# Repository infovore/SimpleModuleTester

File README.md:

# WARNING

**I've never built or tested this. I don't recommend making one of these. It was noodling around.**

# Simple Module Tester

This is a simple Eurorack module tester that can be powered from 5V USB.

- It takes +5v from USB power, and turns it into +/-12v and also passes along the 5v. 
- The key component is a IR0512S DC-DC Converter from XP Power which [costs about £8.50 from Farnell](http://uk.farnell.com/xp-power/ir0512s/dc-dc-converter-semi-reg-dual/dp/1860988) and gives 125mA of power on both rails.  This is a standard SIP package, so other dual output DC-DC converters may work in the same spot. I just chose the one with a good output. 
- The board also includes some simple utilities to test your module with:
  - A square/triangle LFO for use as a clock source and CV input
  - A button that emits a gate from a jack when it is pressed
  - An input jack connected to a bipolar red/green LED for testing output
- Seems to work well with portable USB batteries. 
- The IR0512S is rated 125mA on +12v and -12v, but that seems quite conservative. A Dixie+Turing+Radio Music ran quite happily, with an expected current draw of 160mA on +12v, 52mA on -12v. The converter module was warm but certainly not hot. The whole thing was drawing 600mA from the USB port. 

It is based on Tom Whitwell's [Stupid USB Power][stupidusbpower].

[stupidusbpower]: https://github.com/TomWhitwell/StupidUSBPower

## WHY?

Because you shouldn't test a brand new DIY Euro module by plugging it into $$$ of modular synth. You should test it in isolation.

If you don't have a bipolar bench power supply, that can be hard.

This board seeks to help: it gives you some power outlets for both Eurorack modules and 1U Tiles, some input/output tools to debug CV and gate inputs and outputs, and it's easy to run from battery power.

If you want something more sophisticated, [Olivier Gillet's Module Tester][oliviertester] does a whole lot more and is more refined. It's also more expensive and complex to build.

[oliviertester]: https://github.com/pichenettes/module_tester

## TODO

* add diode/cap/fuse protection
* add two keyed headers
* add M4 standoffs
* make beautiful / useful silkscreen.

## USAGE

1. Seriously: **do not plug this into your computer**. Plug it into a USB battery pack or a mobile phone style mains adaptor
2. **DO NOT PLUG THIS INTO YOUR COMPUTER**

##Tom Whitwell's Reasons why this is stupid: 
1. There are no fuses or protection devices anywhere in the circuit. If you plug this plus $800 worth of modules into a $2000 laptop, you're taking a risk. NB: Do not do this. 
2. There is no filtering in the system, so there will be clock noise from the converter on the rails. The datasheet and my measurements suggest it's in the 60-85khz range. Do not use this to play live or record your new album. 
3. 125mA isn't very much power. Just because the module seems to run above that rating doesn't mean it's safe or reliable.  
4. Keyed headers are not reverse power protection. 

##Status 
- This project is Creative Commmons Licensed [CC-BY-SA](https://creativecommons.org/licenses/by-sa/3.0/). If you like the idea, why not develop it a little and submit your changes here? 
- I haven't exported a formal BOM. The only non-obvious bits aside from the DC-DC converter are: 
    - [USB Socket Type A, Through Hole](http://uk.farnell.com/multicomp/mc32603/usb-2-0-type-a-plug-th/dp/1696544)  
    - [Lumberg  150309 Stereo Socket](http://uk.farnell.com/lumberg/1503-09/connector-rca-jack-3-5mm-3way/dp/1243244)
    - [Amphenol  T821116A1S100CEU  Shrouded headers](http://uk.farnell.com/amphenol/t821116a1s100ceu/header-vertical-2-54mm-16way/dp/2215308)  
    - [Thonkiconn](http://www.thonk.co.uk/shop/thonkiconn-3-5mm-jack-sockets-x50/) mono jack socket, [Alpha](http://www.thonk.co.uk/shop/ttpots/) Pot, 3mm LEDs, 2k LED Resistors, 47uF 16v capacitor on the 5v line.

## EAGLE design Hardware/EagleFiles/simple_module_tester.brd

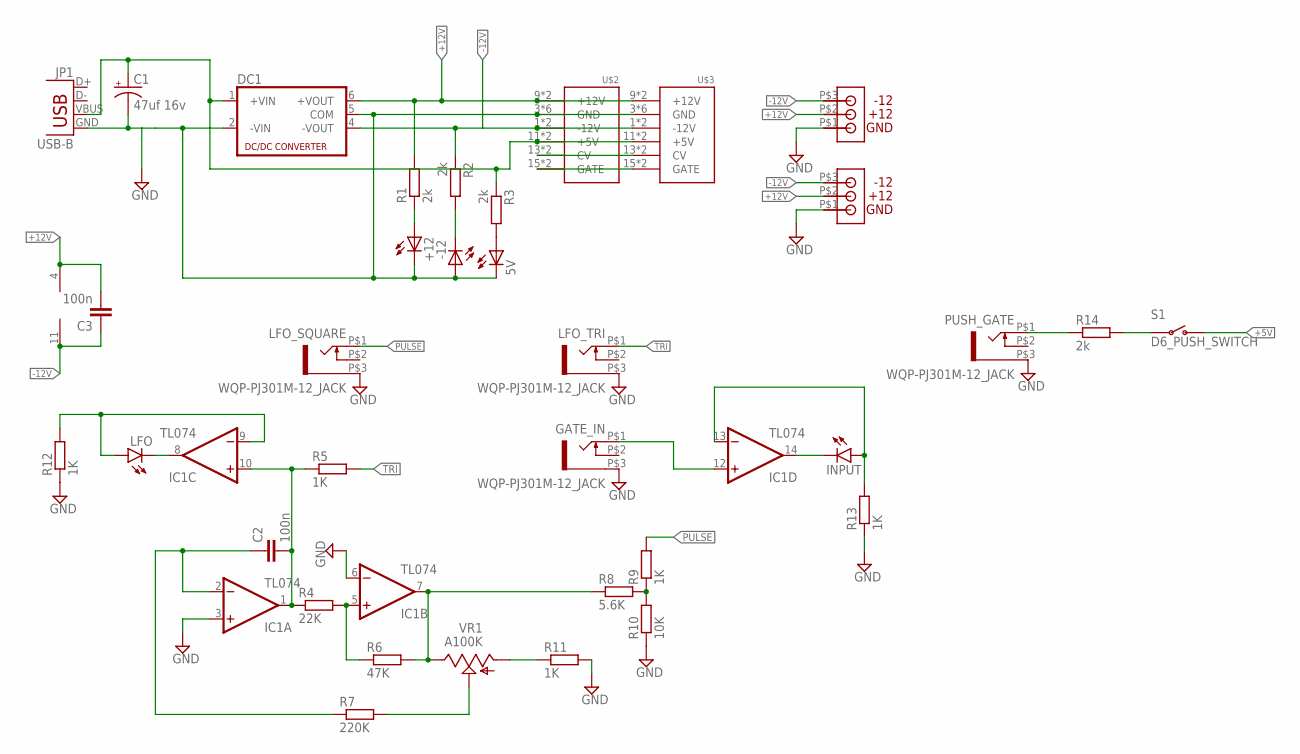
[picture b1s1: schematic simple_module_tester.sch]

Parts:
5V: LED3MM
+12: LED3MM
-12: LED3MM
C1: 47uf 16v; 050_020
C2, C3: 100n; AXIAL-5MM
DC1: NMA
GATE_IN: WQP-PJ301M-12_JACK
IC1: TL074; DIL14
INPUT: LED5MM
JP1: USB-B; USB-B-PTH
LFO: LED5MM
LFO_SQUARE: WQP-PJ301M-12_JACK
LFO_TRI: WQP-PJ301M-12_JACK
PUSH_GATE: WQP-PJ301M-12_JACK
R1, R2, R3, R14: 2k; 7MM_RESISTOR
R4: 22K; 7MM_RESISTOR
R5, R9, R11, R12, R13: 1K; 7MM_RESISTOR
R6: 47K; 7MM_RESISTOR
R7: 220K; 7MM_RESISTOR
R8: 5.6K; 7MM_RESISTOR
R10: 10K; 7MM_RESISTOR
S1: D6_PUSH_SWITCH
U$1, U$4: TILE_POWER_WIDE; THREEPAD_WIDE
U$2, U$3: POWER; POWER_16
VR1: A100K; 9MM_SNAP-IN_POT

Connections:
+5V: C1.+, DC1.1 (+VIN), JP1.VBUS, R3.1, S1.P$1 (O), S1.P$2 (O), U$2.11 (+5V), U$2.12 (+5V), U$3.11 (+5V), U$3.12 (+5V)
+12V: C3.P$2 (2), DC1.6 (+VOUT), IC1.4 (V+), R1.2, U$1.P$2, U$2.9 (+12V), U$2.10 (+12V), U$3.9 (+12V), U$3.10 (+12V), U$4.P$2
-12V: C3.P$1 (1), DC1.4 (-VOUT), IC1.11 (V-), R2.1, U$1.P$3, U$2.1 (-12V), U$2.2 (-12V), U$3.1 (-12V), U$3.2 (-12V), U$4.P$3
GND: 5V.K (C), +12.K (C), -12.A, C1.-, DC1.2 (-VIN), DC1.5 (COM), GATE_IN.P$3 (1), IC1.3 (+IN), IC1.6 (-IN), JP1.GND, LFO_SQUARE.P$3 (1), LFO_TRI.P$3 (1), PUSH_GATE.P$3 (1), R10.1, R11.2, R12.1, R13.1, U$1.P$1, U$2.3 (GND), U$2.4 (GND), U$2.5 (GND), U$2.6 (GND), U$2.7 (GND), U$2.8 (GND), U$3.3 (GND), U$3.4 (GND), U$3.5 (GND), U$3.6 (GND), U$3.7 (GND), U$3.8 (GND), U$4.P$1
unnamed: -12.K (C), R2.2
unnamed: U$2.13 (CV), U$2.14 (CV), U$3.13 (CV), U$3.14 (CV)
unnamed: U$2.15 (GATE), U$2.16 (GATE), U$3.15 (GATE), U$3.16 (GATE)
unnamed: 5V.A, R3.2
unnamed: +12.A, R1.1
unnamed: C2.P$1 (1), IC1.2 (-IN), R7.1
unnamed: IC1.5 (+IN), R4.2, R6.1
unnamed: R7.2, VR1.2 (S)
unnamed: R8.2, R9.1, R10.2
unnamed: IC1.9 (-IN), LFO.A, R12.2
unnamed: C2.P$2 (2), IC1.1 (OUT), IC1.10 (+IN), R4.1, R5.1
unnamed: GATE_IN.P$1 (2), IC1.12 (+IN)
unnamed: IC1.8 (OUT), LFO.K (C)
unnamed: R11.1, VR1.1 (A)
unnamed: IC1.7 (OUT), R6.2, R8.1, VR1.3 (E)
unnamed: IC1.14 (OUT), INPUT.K (C)
unnamed: IC1.13 (-IN), INPUT.A, R13.2
unnamed: PUSH_GATE.P$1 (2), R14.1
unnamed: R14.2, S1.P$3, S1.P$4
PULSE: LFO_SQUARE.P$1 (2), R9.2
TRI: LFO_TRI.P$1 (2), R5.2

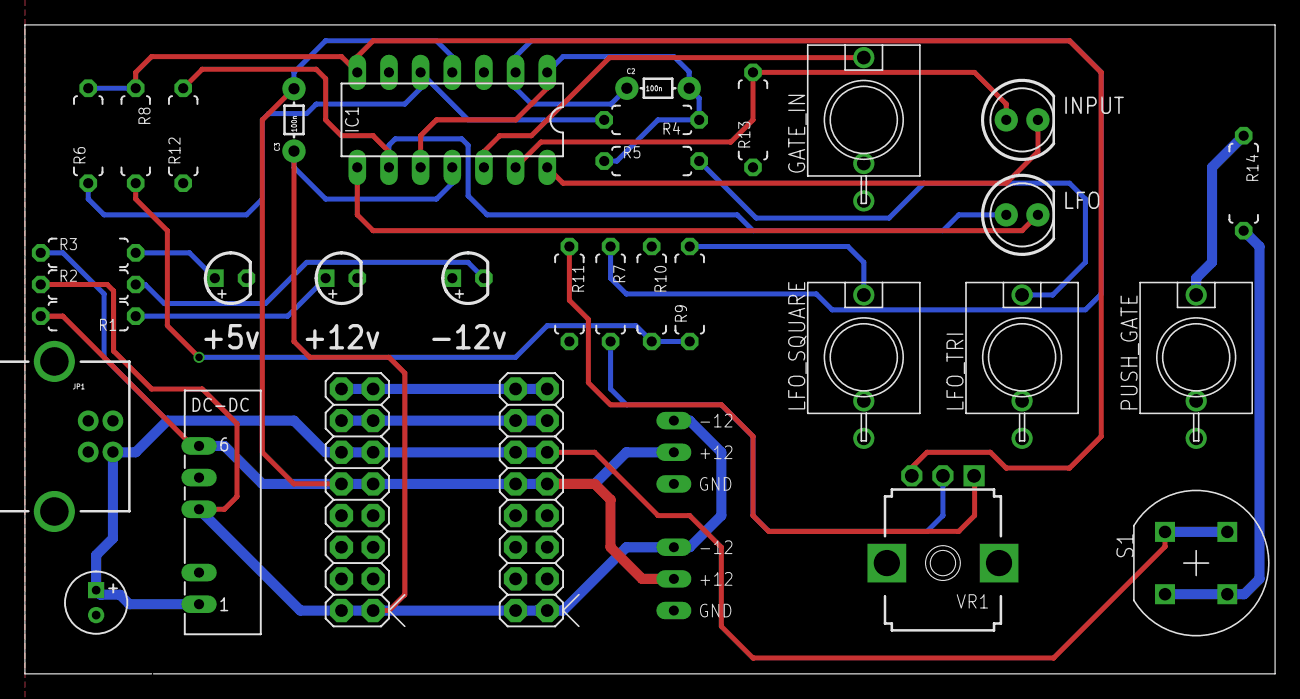
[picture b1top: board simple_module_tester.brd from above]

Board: 4 copper layers, 100.3 x 52.1 mm, 35 parts (0 on the bottom side), 25 nets.

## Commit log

2017-01-06 First pass at adding new functionality.
2017-01-06 Remove Tom W's images.
2017-01-06 WHY.

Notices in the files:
parts and their libraries:
SparkFun-Connectors: Licensing: Creative Commons ShareAlike 4.0 International - https://creativecommons.org/licenses/by-sa/4.0
